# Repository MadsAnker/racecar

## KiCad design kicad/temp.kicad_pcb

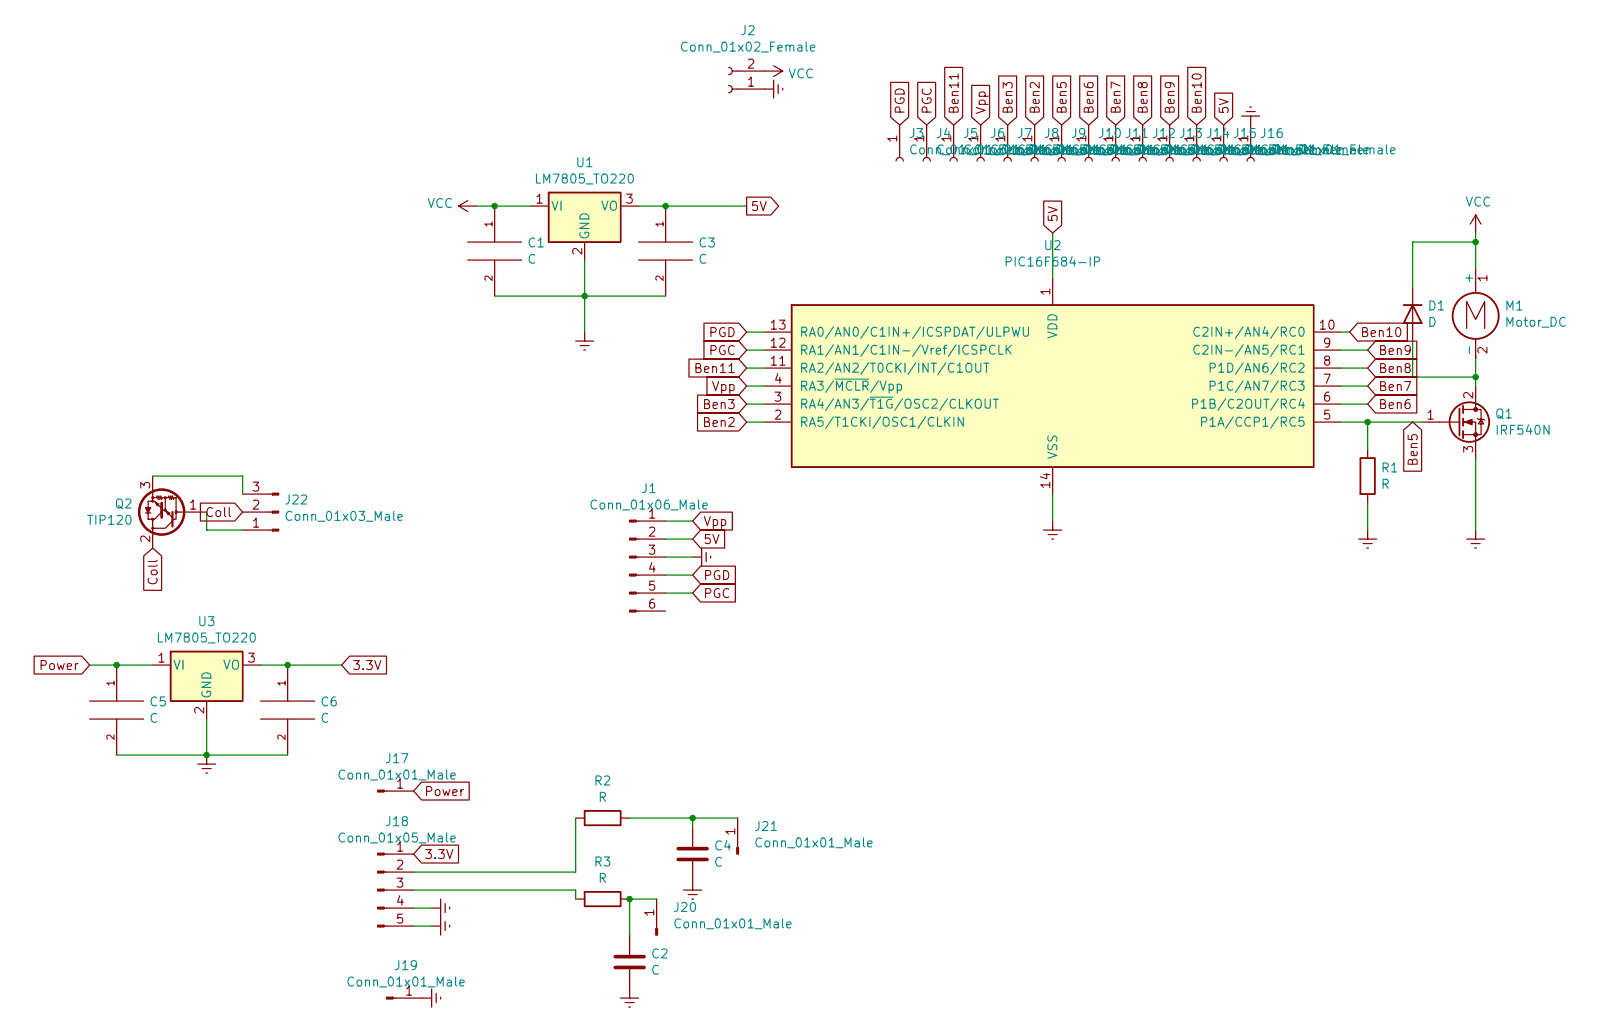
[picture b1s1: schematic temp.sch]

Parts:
C1, C2, C3, C4, C5, C6: C; C_Rect_L7.0mm_W3.5mm_P2.50mm_P5.00mm
D1: D; D_DO-41_SOD81_P10.16mm_Horizontal
J1: Conn_01x06_Male; PinHeader_1x06_P2.54mm_Vertical
J2: Conn_01x02_Female; PinHeader_1x02_P2.54mm_Vertical
J3, J4, J5, J6, J7, J8, J9, J10, J11, J12, J13, J14, J15, J16: Conn_01x01_Female; PinHeader_1x01_P2.54mm_Vertical
J17, J19, J20, J21: Conn_01x01_Male; PinHeader_1x01_P2.54mm_Vertical
J18: Conn_01x05_Male; PinHeader_1x05_P2.54mm_Vertical
J22: Conn_01x03_Male; PinHeader_1x03_P2.54mm_Vertical
M1: Motor_DC; PinHeader_1x02_P2.54mm_Vertical
Q1: IRF540N; TO-220-3_Vertical
Q2: TIP120; TO-220-3_Vertical
R1, R2, R3: R; R_Axial_DIN0207_L6.3mm_D2.5mm_P10.16mm_Horizontal
U1, U3: LM7805_TO220; TO-220-3_Vertical
U2: PIC16F684-IP; DIP-14_W7.62mm_Socket_LongPads

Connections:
3.3V: C6.1, J18.1, U3.3 (VO)
5V: C3.1, J1.2, J15.1, U1.3 (VO), U2.1 (VDD)
Ben2: J8.1, U2.2 (RA5/T1CKI/OSC1/CLKIN)
Ben3: J7.1, U2.3 (RA4/AN3/~T1G~/OSC2/CLKOUT)
Ben5: J9.1, Q1.1 (G), R1.1, U2.5 (P1A/CCP1/RC5)
Ben6: J10.1, U2.6 (P1B/C2OUT/RC4)
Ben7: J11.1, U2.7 (P1C/AN7/RC3)
Ben8: J12.1, U2.8 (P1D/AN6/RC2)
Ben9: J13.1, U2.9 (C2IN-/AN5/RC1)
Ben10: J14.1, U2.10 (C2IN+/AN4/RC0)
Ben11: J5.1, U2.11 (RA2/AN2/T0CKI/INT/C1OUT)
Coll: J22.2, Q2.2 (C)
Earth: C1.2, C2.1, C3.2, C4.1, C5.2, C6.2, J1.3, J2.1, J16.1, J18.4, J18.5, J19.1, Q1.3 (S), R1.2, U1.2 (GND), U2.14 (VSS), U3.2 (GND)
unnamed: C2.2, J20.1, R3.1
unnamed: C4.2, J21.1, R2.1
unnamed: D1.2 (A), M1.2 (-), Q1.2 (D)
unnamed: J18.2, R2.2
unnamed: J18.3, R3.2
unnamed: J22.1, Q2.1 (B)
unnamed: J22.3, Q2.3 (E)
PGC: J1.5, J4.1, U2.12 (RA1/AN1/C1IN-/Vref/ICSPCLK)
PGD: J1.4, J3.1, U2.13 (RA0/AN0/C1IN+/ICSPDAT/ULPWU)
Power: C5.1, J17.1, U3.1 (VI)
VCC: C1.1, D1.1 (K), J2.2, M1.1 (+), U1.1 (VI)
Vpp: J1.1, J6.1, U2.4 (RA3/~MCLR~/Vpp)

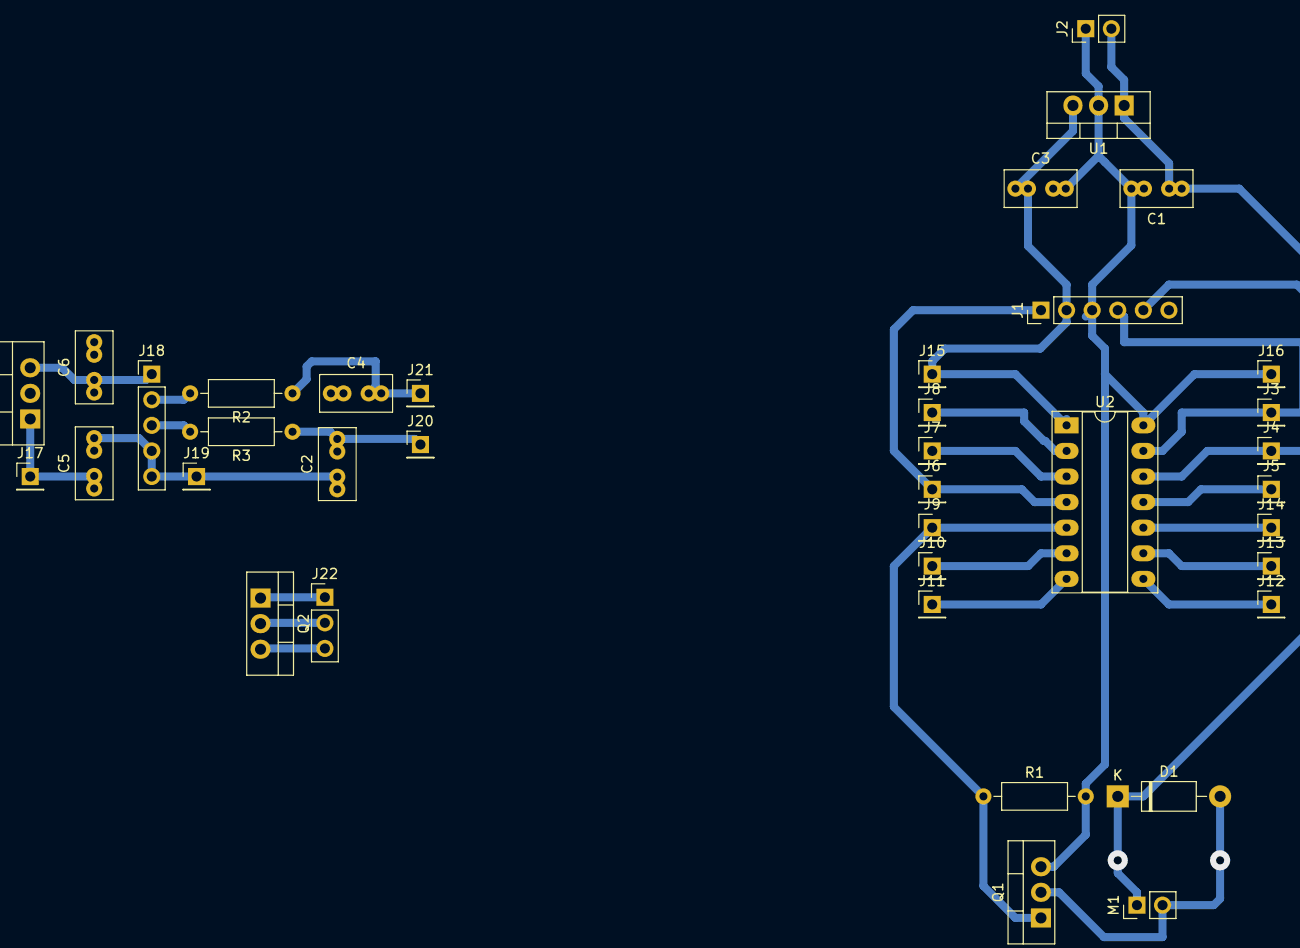
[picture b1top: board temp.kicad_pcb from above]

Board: 2 copper layers, 38 parts (0 on the bottom side), 25 nets.

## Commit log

2020-11-23 init
2020-11-24 add mplab project
2020-11-30 kicad
2020-12-04 add accel pcb
2020-12-04 kortslut modul
2020-12-11 12-3.3V converter
